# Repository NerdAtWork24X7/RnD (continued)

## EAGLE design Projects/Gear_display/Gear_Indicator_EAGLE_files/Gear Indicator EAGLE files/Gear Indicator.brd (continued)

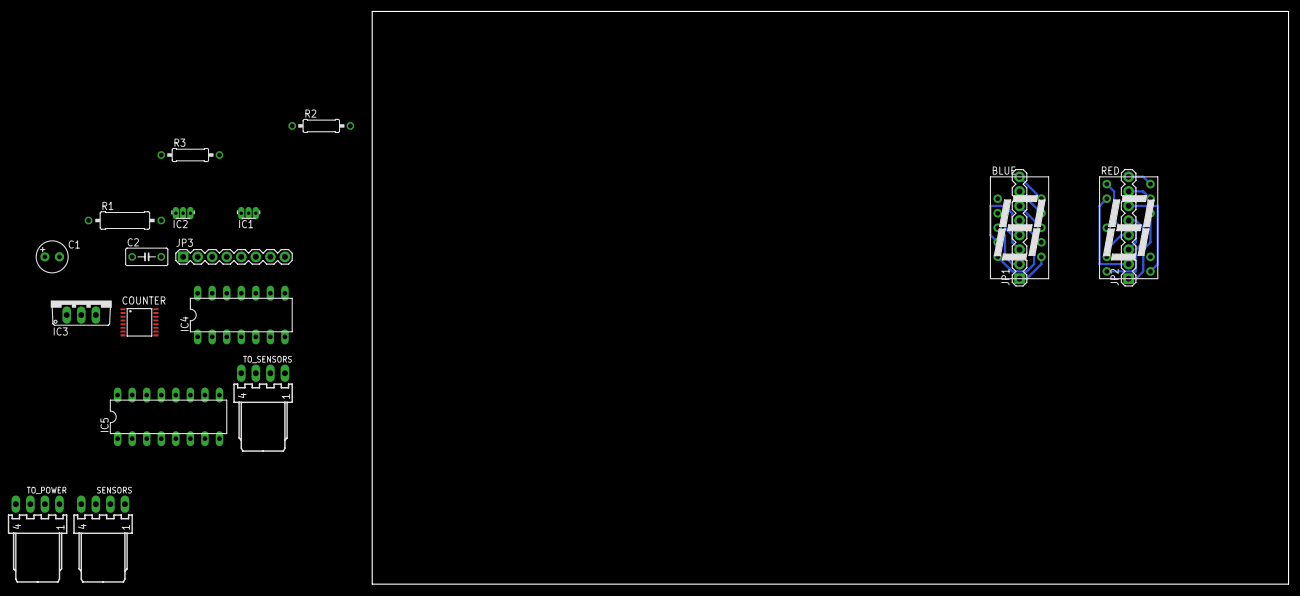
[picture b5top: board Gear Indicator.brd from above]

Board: 2 copper layers, 160.0 x 100.0 mm, 19 parts (0 on the bottom side), 38 nets.

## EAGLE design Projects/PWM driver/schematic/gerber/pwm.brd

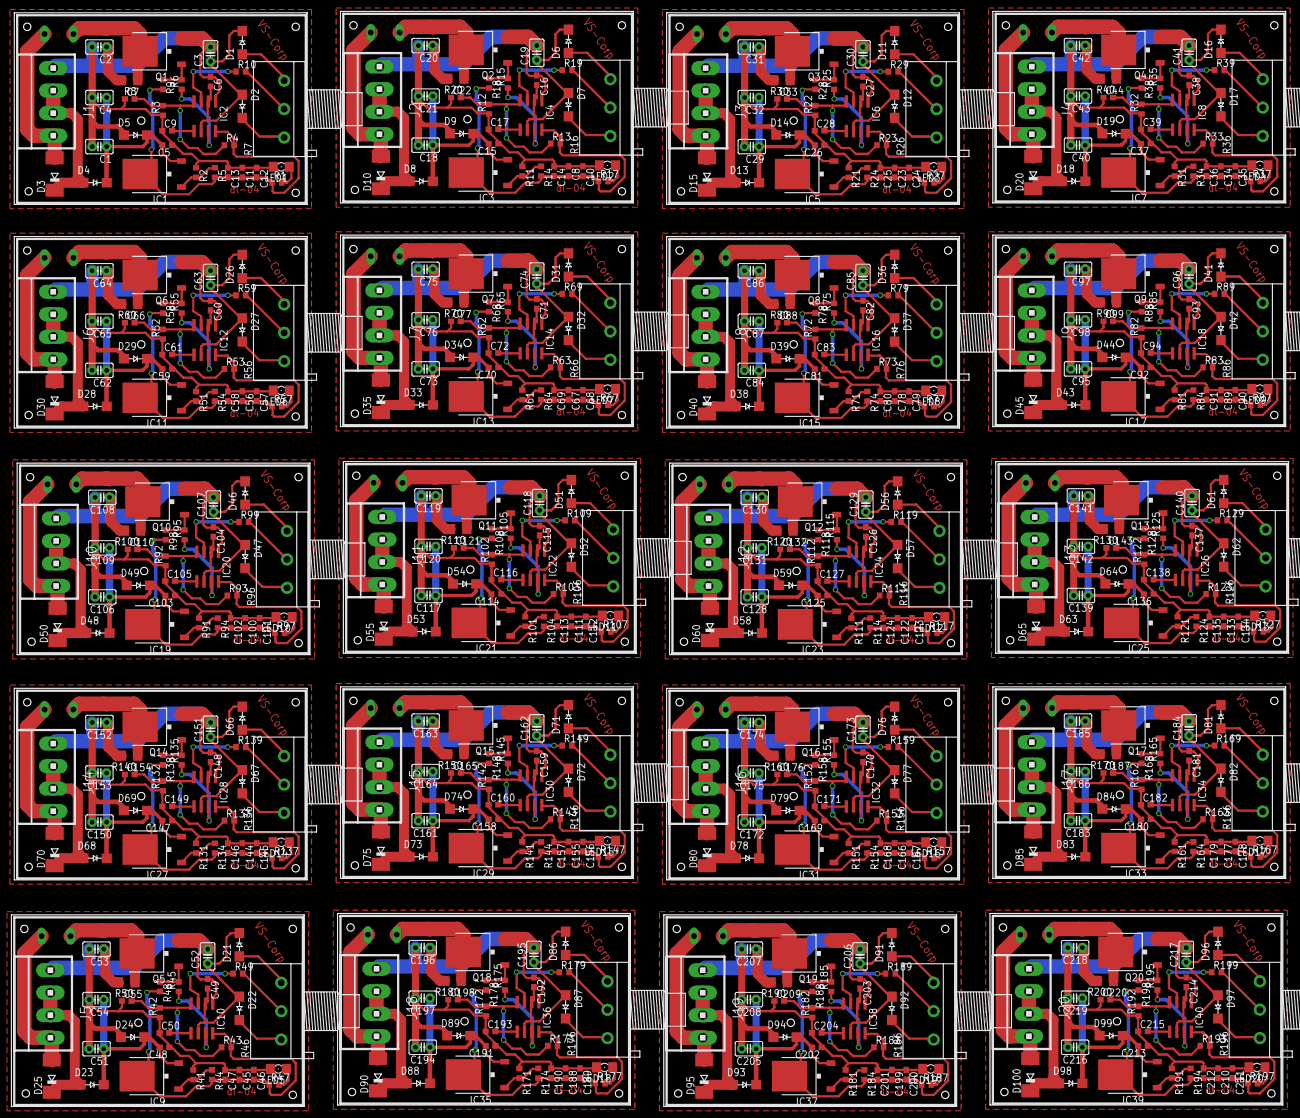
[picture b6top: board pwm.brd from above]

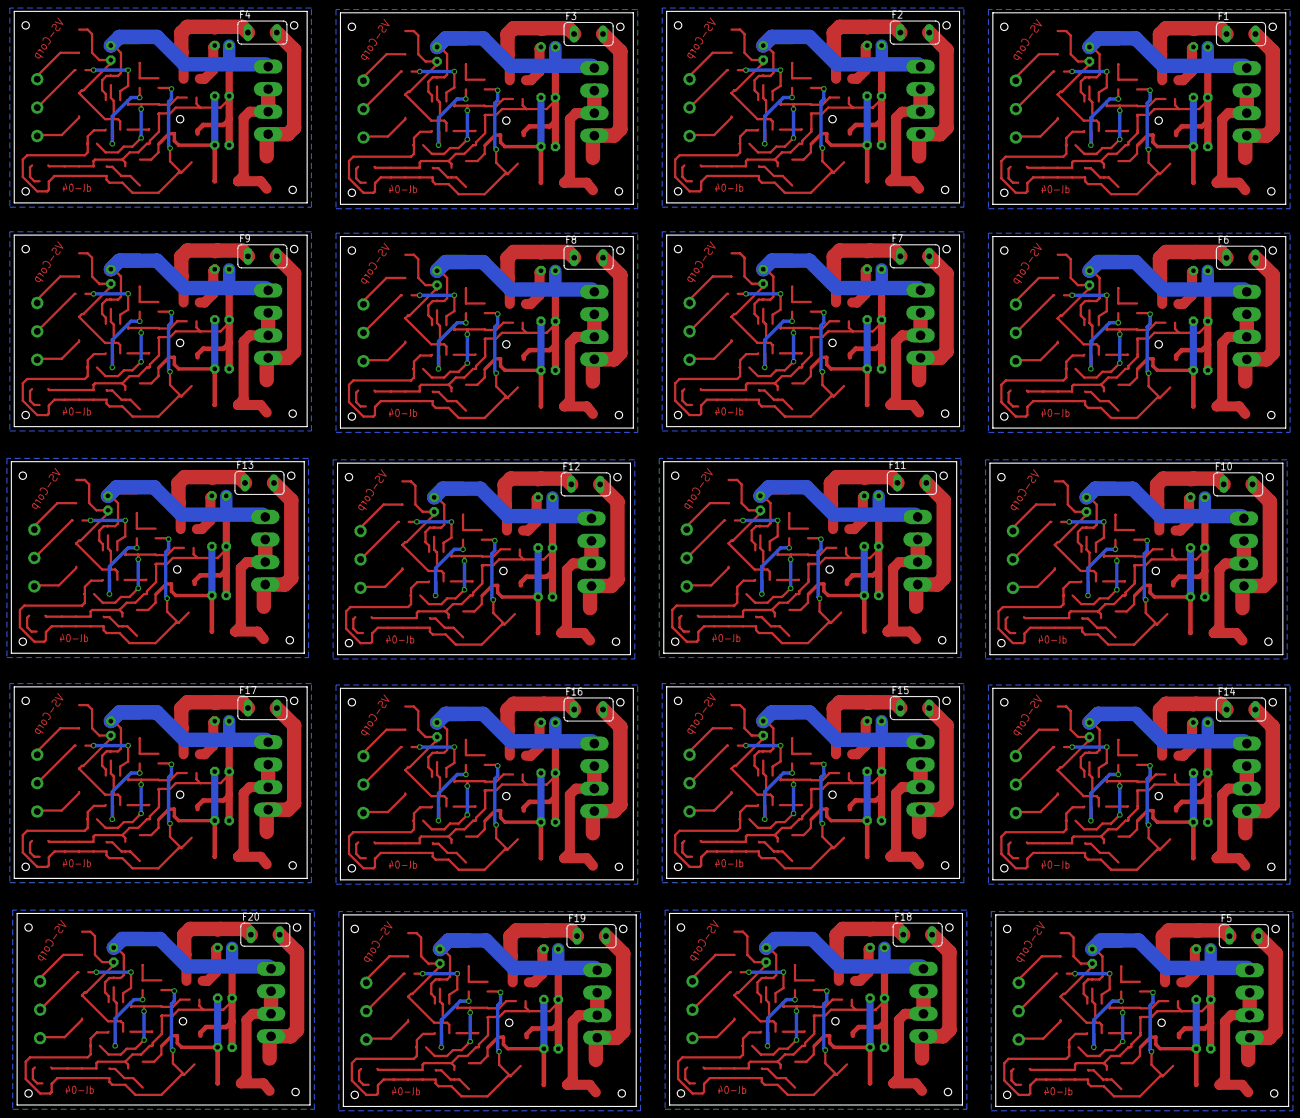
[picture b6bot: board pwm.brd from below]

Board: 2 copper layers, 224.8 x 192.7 mm, 640 parts (20 on the bottom side), 360 nets.

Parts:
C1, C18, C29, C40, C51, C62, C73, C84, C95, C106, C117, C128, C139, C150, C161, C172, C183, C194, C205, C216: C025-025X050
C2, C20, C31, C42, C53, C64, C75, C86, C97, C108, C119, C130, C141, C152, C163, C174, C185, C196, C207, C218: 2.2uf; C025-025X050
C3, C19, C30, C41, C52, C63, C74, C85, C96, C107, C118, C129, C140, C151, C162, C173, C184, C195, C206, C217: 0.1uf; C025-025X050
C4, C21, C32, C43, C54, C65, C76, C87, C98, C109, C120, C131, C142, C153, C164, C175, C186, C197, C208, C219: 220uf; C025-025X050
C5, C15, C26, C37, C48, C59, C70, C81, C92, C103, C114, C125, C136, C147, C158, C169, C180, C191, C202, C213: 100nf; C0603
C6, C16, C27, C38, C49, C60, C71, C82, C93, C104, C115, C126, C137, C148, C159, C170, C181, C192, C203, C214: 0.1uF; C0603
C7, C22, C33, C44, C55, C66, C77, C88, C99, C110, C121, C132, C143, C154, C165, C176, C187, C198, C209, C220: 220uf; C0603
C8, C11, C23, C34, C45, C56, C67, C78, C89, C100, C111, C122, C133, C144, C155, C166, C177, C188, C199, C210: 100nF; C0603
C9, C10, C12, C17, C24, C28, C35, C39, C46, C50, C57, C61, C68, C72, C79, C83, C90, C94, C101, C105, C112, C116, C123, C127, C134, C138, C145, C149, C156, C160, C167, C171, C178, C182, C189, C193, C200, C204, C211, C215: 10nF; C0603
C13, C14, C25, C36, C47, C58, C69, C80, C91, C102, C113, C124, C135, C146, C157, C168, C179, C190, C201, C212: 1uF; C0603
D1, D2, D6, D7, D11, D12, D16, D17, D21, D22, D26, D27, D31, D32, D36, D37, D41, D42, D46, D47, D51, D52, D56, D57, D61, D62, D66, D67, D71, D72, D76, D77, D81, D82, D86, D87, D91, D92, D96, D97: FM4007; SMA-DO214AC
D3, D10, D15, D20, D25, D30, D35, D40, D45, D50, D55, D60, D65, D70, D75, D80, D85, D90, D95, D100: SOD106-W
D4, D8, D13, D18, D23, D28, D33, D38, D43, D48, D53, D58, D63, D68, D73, D78, D83, D88, D93, D98: Fm4007; SMA-DO214AC
D5, D9, D14, D19, D24, D29, D34, D39, D44, D49, D54, D59, D64, D69, D74, D79, D84, D89, D94, D99: 1N34; SMA-DO214AC
F1, F2, F3, F4, F5, F6, F7, F8, F9, F10, F11, F12, F13, F14, F15, F16, F17, F18, F19, F20: FUSETE5; TE5
IC1, IC3, IC5, IC7, IC9, IC11, IC13, IC15, IC17, IC19, IC21, IC23, IC25, IC27, IC29, IC31, IC33, IC35, IC37, IC39: 317; DPACK
IC2, IC4, IC6, IC8, IC10, IC12, IC14, IC16, IC18, IC20, IC22, IC24, IC26, IC28, IC30, IC32, IC34, IC36, IC38, IC40: LM555D; SO08
J1, J2, J3, J4, J5, J6, J7, J8, J9, J10, J11, J12, J13, J14, J15, J16, J17, J18, J19, J20: 1X4MTA
LED1, LED2, LED3, LED4, LED5, LED6, LED7, LED8, LED9, LED10, LED11, LED12, LED13, LED14, LED15, LED16, LED17, LED18, LED19, LED20: LED_1206
Q1, Q2, Q3, Q4, Q5, Q6, Q7, Q8, Q9, Q10, Q11, Q12, Q13, Q14, Q15, Q16, Q17, Q18, Q19, Q20: FDD4141TO252; TO252
R1, R5, R14, R17, R24, R27, R34, R37, R44, R47, R54, R57, R64, R67, R74, R77, R84, R87, R94, R97, R104, R107, R114, R117, R124, R127, R134, R137, R144, R147, R154, R157, R164, R167, R174, R177, R184, R187, R194, R197: 470; R0603
R2, R11, R21, R31, R41, R51, R61, R71, R81, R91, R101, R111, R121, R131, R141, R151, R161, R171, R181, R191: 1.5k; R0603
R3, R12, R22, R32, R42, R52, R62, R72, R82, R92, R102, R112, R122, R132, R142, R152, R162, R172, R182, R192: 330k; R0603
R4, R13, R23, R33, R43, R53, R63, R73, R83, R93, R103, R113, R123, R133, R143, R153, R163, R173, R183, R193: 150k; R0603
R6, R15, R25, R35, R45, R55, R65, R75, R85, R95, R105, R115, R125, R135, R145, R155, R165, R175, R185, R195: 1k; R0603
R7, R16, R26, R36, R46, R56, R66, R76, R86, R96, R106, R116, R126, R136, R146, R156, R166, R176, R186, R196: 3RP/1610N
R8, R20, R30, R40, R50, R60, R70, R80, R90, R100, R110, R120, R130, R140, R150, R160, R170, R180, R190, R200: 100; R1206
R9, R18, R28, R38, R48, R58, R68, R78, R88, R98, R108, R118, R128, R138, R148, R158, R168, R178, R188, R198: 47k; R0603
R10, R19, R29, R39, R49, R59, R69, R79, R89, R99, R109, R119, R129, R139, R149, R159, R169, R179, R189, R199: 0r0; R0603

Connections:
GND: C1.2, C2.2, C3.2, C4.2, C5.1, C6.1, C7.1, C9.1, C11.1, C12.1, C13.1, D5.A, IC2.1, J1.1, LED1.C, Q1.2, R2.1, R3.1
GND1: C8.1, C10.1, C14.1, C15.1, C16.1, C17.1, C18.2, C19.2, C20.2, C21.2, C22.1, D9.A, IC4.1, J2.1, LED2.C, Q2.2, R11.1, R12.1
GND2: C23.1, C24.1, C25.1, C26.1, C27.1, C28.1, C29.2, C30.2, C31.2, C32.2, C33.1, D14.A, IC6.1, J3.1, LED3.C, Q3.2, R21.1, R22.1
GND3: C34.1, C35.1, C36.1, C37.1, C38.1, C39.1, C40.2, C41.2, C42.2, C43.2, C44.1, D19.A, IC8.1, J4.1, LED4.C, Q4.2, R31.1, R32.1
GND4: C45.1, C46.1, C47.1, C48.1, C49.1, C50.1, C51.2, C52.2, C53.2, C54.2, C55.1, D24.A, IC10.1, J5.1, LED5.C, Q5.2, R41.1, R42.1
GND5: C56.1, C57.1, C58.1, C59.1, C60.1, C61.1, C62.2, C63.2, C64.2, C65.2, C66.1, D29.A, IC12.1, J6.1, LED6.C, Q6.2, R51.1, R52.1
GND6: C67.1, C68.1, C69.1, C70.1, C71.1, C72.1, C73.2, C74.2, C75.2, C76.2, C77.1, D34.A, IC14.1, J7.1, LED7.C, Q7.2, R61.1, R62.1
GND7: C78.1, C79.1, C80.1, C81.1, C82.1, C83.1, C84.2, C85.2, C86.2, C87.2, C88.1, D39.A, IC16.1, J8.1, LED8.C, Q8.2, R71.1, R72.1
GND8: C89.1, C90.1, C91.1, C92.1, C93.1, C94.1, C95.2, C96.2, C97.2, C98.2, C99.1, D44.A, IC18.1, J9.1, LED9.C, Q9.2, R81.1, R82.1
GND9: C100.1, C101.1, C102.1, C103.1, C104.1, C105.1, C106.2, C107.2, C108.2, C109.2, C110.1, D49.A, IC20.1, J10.1, LED10.C, Q10.2, R91.1, R92.1
GND10: C111.1, C112.1, C113.1, C114.1, C115.1, C116.1, C117.2, C118.2, C119.2, C120.2, C121.1, D54.A, IC22.1, J11.1, LED11.C, Q11.2, R101.1, R102.1
GND11: C122.1, C123.1, C124.1, C125.1, C126.1, C127.1, C128.2, C129.2, C130.2, C131.2, C132.1, D59.A, IC24.1, J12.1, LED12.C, Q12.2, R111.1, R112.1
GND12: C133.1, C134.1, C135.1, C136.1, C137.1, C138.1, C139.2, C140.2, C141.2, C142.2, C143.1, D64.A, IC26.1, J13.1, LED13.C, Q13.2, R121.1, R122.1
GND13: C144.1, C145.1, C146.1, C147.1, C148.1, C149.1, C150.2, C151.2, C152.2, C153.2, C154.1, D69.A, IC28.1, J14.1, LED14.C, Q14.2, R131.1, R132.1
GND14: C155.1, C156.1, C157.1, C158.1, C159.1, C160.1, C161.2, C162.2, C163.2, C164.2, C165.1, D74.A, IC30.1, J15.1, LED15.C, Q15.2, R141.1, R142.1
GND15: C166.1, C167.1, C168.1, C169.1, C170.1, C171.1, C172.2, C173.2, C174.2, C175.2, C176.1, D79.A, IC32.1, J16.1, LED16.C, Q16.2, R151.1, R152.1
GND16: C177.1, C178.1, C179.1, C180.1, C181.1, C182.1, C183.2, C184.2, C185.2, C186.2, C187.1, D84.A, IC34.1, J17.1, LED17.C, Q17.2, R161.1, R162.1
GND17: C188.1, C189.1, C190.1, C191.1, C192.1, C193.1, C194.2, C195.2, C196.2, C197.2, C198.1, D89.A, IC36.1, J18.1, LED18.C, Q18.2, R171.1, R172.1
GND18: C199.1, C200.1, C201.1, C202.1, C203.1, C204.1, C205.2, C206.2, C207.2, C208.2, C209.1, D94.A, IC38.1, J19.1, LED19.C, Q19.2, R181.1, R182.1
GND19: C210.1, C211.1, C212.1, C213.1, C214.1, C215.1, C216.2, C217.2, C218.2, C219.2, C220.1, D99.A, IC40.1, J20.1, LED20.C, Q20.2, R191.1, R192.1
unnamed: C7.2, IC2.4, R3.2, R4.1
unnamed: C3.1, C6.2, D1.K, D2.A, IC2.2, IC2.6
unnamed: D1.A, R7.3
unnamed: D2.K, R7.1
unnamed: R7.2, R10.2
unnamed: IC2.3, R10.1
unnamed: C9.2, IC2.5
unnamed: C1.1, C4.1, C5.2, D4.K, D5.K, IC1.VIN
unnamed: Q1.1, R6.2, R9.1
unnamed: IC2.7, R6.1
unnamed: LED1.A, R1.2
unnamed: C2.1, R8.2
unnamed: IC1.ADJ, R2.2, R5.1
unnamed: F1.1, Q1.3, R8.1
unnamed: D3.A, F1.2, J1.4
unnamed: D6.A, R16.3
unnamed: D7.K, R16.1
unnamed: C17.2, IC4.5
unnamed: C16.2, C19.1, D6.K, D7.A, IC4.2, IC4.6
unnamed: Q2.1, R15.2, R18.1
unnamed: C22.2, IC4.4, R12.2, R13.1
unnamed: IC4.3, R19.1
unnamed: IC4.7, R15.1
unnamed: C15.2, C18.1, C21.1, D8.K, D9.K, IC3.VIN
unnamed: LED2.A, R17.2
unnamed: IC3.ADJ, R11.2, R14.1
unnamed: F2.1, Q2.3, R20.1
unnamed: D10.A, F2.2, J2.4
unnamed: R16.2, R19.2
unnamed: C20.1, R20.2
unnamed: D11.A, R26.3
unnamed: D12.K, R26.1
unnamed: C28.2, IC6.5
unnamed: C27.2, C30.1, D11.K, D12.A, IC6.2, IC6.6
unnamed: Q3.1, R25.2, R28.1
unnamed: C33.2, IC6.4, R22.2, R23.1
unnamed: IC6.3, R29.1
unnamed: IC6.7, R25.1
unnamed: C26.2, C29.1, C32.1, D13.K, D14.K, IC5.VIN
unnamed: LED3.A, R27.2
unnamed: IC5.ADJ, R21.2, R24.1
unnamed: F3.1, Q3.3, R30.1
unnamed: D15.A, F3.2, J3.4
unnamed: R26.2, R29.2
unnamed: C31.1, R30.2
unnamed: D16.A, R36.3
unnamed: D17.K, R36.1
unnamed: C39.2, IC8.5
unnamed: C38.2, C41.1, D16.K, D17.A, IC8.2, IC8.6
unnamed: Q4.1, R35.2, R38.1
unnamed: C44.2, IC8.4, R32.2, R33.1
unnamed: IC8.3, R39.1
unnamed: IC8.7, R35.1
unnamed: C37.2, C40.1, C43.1, D18.K, D19.K, IC7.VIN
unnamed: LED4.A, R37.2
unnamed: IC7.ADJ, R31.2, R34.1
unnamed: F4.1, Q4.3, R40.1
unnamed: D20.A, F4.2, J4.4
unnamed: R36.2, R39.2
unnamed: C42.1, R40.2
unnamed: D21.A, R46.3
unnamed: D22.K, R46.1
unnamed: C50.2, IC10.5
unnamed: C49.2, C52.1, D21.K, D22.A, IC10.2, IC10.6
unnamed: Q5.1, R45.2, R48.1
unnamed: C55.2, IC10.4, R42.2, R43.1
unnamed: IC10.3, R49.1
unnamed: IC10.7, R45.1
unnamed: C48.2, C51.1, C54.1, D23.K, D24.K, IC9.VIN
unnamed: LED5.A, R47.2
unnamed: IC9.ADJ, R41.2, R44.1
unnamed: F5.1, Q5.3, R50.1
unnamed: D25.A, F5.2, J5.4
unnamed: R46.2, R49.2
unnamed: C53.1, R50.2
unnamed: D26.A, R56.3
unnamed: D27.K, R56.1
unnamed: C61.2, IC12.5
unnamed: C60.2, C63.1, D26.K, D27.A, IC12.2, IC12.6
unnamed: Q6.1, R55.2, R58.1
unnamed: C66.2, IC12.4, R52.2, R53.1
unnamed: IC12.3, R59.1
unnamed: IC12.7, R55.1
unnamed: C59.2, C62.1, C65.1, D28.K, D29.K, IC11.VIN
unnamed: LED6.A, R57.2
unnamed: IC11.ADJ, R51.2, R54.1
unnamed: F6.1, Q6.3, R60.1
unnamed: D30.A, F6.2, J6.4
unnamed: R56.2, R59.2
unnamed: C64.1, R60.2
unnamed: D31.A, R66.3
unnamed: D32.K, R66.1
unnamed: C72.2, IC14.5
unnamed: C71.2, C74.1, D31.K, D32.A, IC14.2, IC14.6
unnamed: Q7.1, R65.2, R68.1
unnamed: C77.2, IC14.4, R62.2, R63.1
unnamed: IC14.3, R69.1
unnamed: IC14.7, R65.1
unnamed: C70.2, C73.1, C76.1, D33.K, D34.K, IC13.VIN
unnamed: LED7.A, R67.2
unnamed: IC13.ADJ, R61.2, R64.1
unnamed: F7.1, Q7.3, R70.1
unnamed: D35.A, F7.2, J7.4
unnamed: R66.2, R69.2
unnamed: C75.1, R70.2
unnamed: D36.A, R76.3
unnamed: D37.K, R76.1
unnamed: C83.2, IC16.5
unnamed: C82.2, C85.1, D36.K, D37.A, IC16.2, IC16.6
unnamed: Q8.1, R75.2, R78.1
unnamed: C88.2, IC16.4, R72.2, R73.1
unnamed: IC16.3, R79.1
unnamed: IC16.7, R75.1
unnamed: C81.2, C84.1, C87.1, D38.K, D39.K, IC15.VIN
unnamed: LED8.A, R77.2
unnamed: IC15.ADJ, R71.2, R74.1
unnamed: F8.1, Q8.3, R80.1
unnamed: D40.A, F8.2, J8.4
unnamed: R76.2, R79.2
unnamed: C86.1, R80.2
unnamed: D41.A, R86.3
unnamed: D42.K, R86.1
unnamed: C94.2, IC18.5
unnamed: C93.2, C96.1, D41.K, D42.A, IC18.2, IC18.6
unnamed: Q9.1, R85.2, R88.1
unnamed: C99.2, IC18.4, R82.2, R83.1
unnamed: IC18.3, R89.1
unnamed: IC18.7, R85.1
unnamed: C92.2, C95.1, C98.1, D43.K, D44.K, IC17.VIN
unnamed: LED9.A, R87.2
unnamed: IC17.ADJ, R81.2, R84.1
unnamed: F9.1, Q9.3, R90.1
unnamed: D45.A, F9.2, J9.4
unnamed: D46.A, R96.3
unnamed: D47.K, R96.1
unnamed: C105.2, IC20.5
unnamed: C104.2, C107.1, D46.K, D47.A, IC20.2, IC20.6
unnamed: Q10.1, R95.2, R98.1
unnamed: C110.2, IC20.4, R92.2, R93.1
unnamed: IC20.3, R99.1
unnamed: IC20.7, R95.1
unnamed: C103.2, C106.1, C109.1, D48.K, D49.K, IC19.VIN
unnamed: LED10.A, R97.2
unnamed: IC19.ADJ, R91.2, R94.1
unnamed: F10.1, Q10.3, R100.1
unnamed: D50.A, F10.2, J10.4
unnamed: R96.2, R99.2
unnamed: C108.1, R100.2
unnamed: D51.A, R106.3
unnamed: D52.K, R106.1
unnamed: C116.2, IC22.5
unnamed: C115.2, C118.1, D51.K, D52.A, IC22.2, IC22.6
unnamed: Q11.1, R105.2, R108.1
unnamed: C121.2, IC22.4, R102.2, R103.1
unnamed: IC22.3, R109.1
unnamed: IC22.7, R105.1
unnamed: C114.2, C117.1, C120.1, D53.K, D54.K, IC21.VIN
unnamed: LED11.A, R107.2
unnamed: IC21.ADJ, R101.2, R104.1
unnamed: F11.1, Q11.3, R110.1
unnamed: D55.A, F11.2, J11.4
unnamed: R106.2, R109.2
unnamed: C119.1, R110.2
unnamed: R86.2, R89.2
unnamed: C97.1, R90.2
unnamed: D56.A, R116.3
unnamed: D57.K, R116.1
unnamed: C127.2, IC24.5
unnamed: C126.2, C129.1, D56.K, D57.A, IC24.2, IC24.6
unnamed: Q12.1, R115.2, R118.1
unnamed: C132.2, IC24.4, R112.2, R113.1
unnamed: IC24.3, R119.1
unnamed: IC24.7, R115.1
unnamed: C125.2, C128.1, C131.1, D58.K, D59.K, IC23.VIN
unnamed: LED12.A, R117.2
unnamed: IC23.ADJ, R111.2, R114.1
unnamed: F12.1, Q12.3, R120.1
unnamed: D60.A, F12.2, J12.4
unnamed: R116.2, R119.2
unnamed: C130.1, R120.2
unnamed: D61.A, R126.3
unnamed: D62.K, R126.1
unnamed: C138.2, IC26.5
unnamed: C137.2, C140.1, D61.K, D62.A, IC26.2, IC26.6
unnamed: Q13.1, R125.2, R128.1
unnamed: C143.2, IC26.4, R122.2, R123.1
unnamed: IC26.3, R129.1
unnamed: IC26.7, R125.1
unnamed: C136.2, C139.1, C142.1, D63.K, D64.K, IC25.VIN
unnamed: LED13.A, R127.2
unnamed: IC25.ADJ, R121.2, R124.1
unnamed: D66.A, R136.3
unnamed: D67.K, R136.1
unnamed: C149.2, IC28.5
unnamed: C148.2, C151.1, D66.K, D67.A, IC28.2, IC28.6
unnamed: Q14.1, R135.2, R138.1
unnamed: C154.2, IC28.4, R132.2, R133.1
unnamed: IC28.3, R139.1
unnamed: IC28.7, R135.1
unnamed: C147.2, C150.1, C153.1, D68.K, D69.K, IC27.VIN
unnamed: LED14.A, R137.2
unnamed: IC27.ADJ, R131.2, R134.1
unnamed: F14.1, Q14.3, R140.1
unnamed: D70.A, F14.2, J14.4
unnamed: R136.2, R139.2
unnamed: C152.1, R140.2
unnamed: D71.A, R146.3
unnamed: D72.K, R146.1
unnamed: C160.2, IC30.5
unnamed: C159.2, C162.1, D71.K, D72.A, IC30.2, IC30.6
unnamed: Q15.1, R145.2, R148.1
unnamed: C165.2, IC30.4, R142.2, R143.1
unnamed: IC30.3, R149.1
unnamed: IC30.7, R145.1
unnamed: C158.2, C161.1, C164.1, D73.K, D74.K, IC29.VIN
unnamed: LED15.A, R147.2
unnamed: IC29.ADJ, R141.2, R144.1
unnamed: F15.1, Q15.3, R150.1
unnamed: D75.A, F15.2, J15.4
unnamed: R146.2, R149.2
unnamed: C163.1, R150.2
unnamed: F13.1, Q13.3, R130.1
unnamed: D65.A, F13.2, J13.4
unnamed: R126.2, R129.2
unnamed: C141.1, R130.2
unnamed: D76.A, R156.3
unnamed: D77.K, R156.1
unnamed: C171.2, IC32.5
unnamed: C170.2, C173.1, D76.K, D77.A, IC32.2, IC32.6
unnamed: Q16.1, R155.2, R158.1
unnamed: C176.2, IC32.4, R152.2, R153.1
unnamed: IC32.3, R159.1
unnamed: IC32.7, R155.1
unnamed: C169.2, C172.1, C175.1, D78.K, D79.K, IC31.VIN
unnamed: LED16.A, R157.2
unnamed: IC31.ADJ, R151.2, R154.1
unnamed: F16.1, Q16.3, R160.1
unnamed: D80.A, F16.2, J16.4
unnamed: R156.2, R159.2
unnamed: C174.1, R160.2
unnamed: D81.A, R166.3
unnamed: D82.K, R166.1
unnamed: C182.2, IC34.5
unnamed: C181.2, C184.1, D81.K, D82.A, IC34.2, IC34.6
unnamed: Q17.1, R165.2, R168.1
unnamed: C187.2, IC34.4, R162.2, R163.1
unnamed: IC34.3, R169.1
unnamed: IC34.7, R165.1
unnamed: C180.2, C183.1, C186.1, D83.K, D84.K, IC33.VIN
unnamed: D86.A, R176.3
unnamed: D87.K, R176.1
unnamed: C193.2, IC36.5
unnamed: C192.2, C195.1, D86.K, D87.A, IC36.2, IC36.6
unnamed: Q18.1, R175.2, R178.1
unnamed: C198.2, IC36.4, R172.2, R173.1
unnamed: IC36.3, R179.1
unnamed: IC36.7, R175.1
unnamed: C191.2, C194.1, C197.1, D88.K, D89.K, IC35.VIN
unnamed: LED18.A, R177.2
unnamed: IC35.ADJ, R171.2, R174.1
unnamed: F18.1, Q18.3, R180.1
unnamed: D90.A, F18.2, J18.4
unnamed: R176.2, R179.2
unnamed: C196.1, R180.2
unnamed: LED17.A, R167.2
unnamed: IC33.ADJ, R161.2, R164.1
unnamed: F17.1, Q17.3, R170.1
unnamed: D85.A, F17.2, J17.4
unnamed: R166.2, R169.2
unnamed: C185.1, R170.2
unnamed: D91.A, R186.3
unnamed: D92.K, R186.1
unnamed: C204.2, IC38.5
unnamed: C203.2, C206.1, D91.K, D92.A, IC38.2, IC38.6
unnamed: Q19.1, R185.2, R188.1
unnamed: C209.2, IC38.4, R182.2, R183.1
unnamed: IC38.3, R189.1
unnamed: IC38.7, R185.1
unnamed: C202.2, C205.1, C208.1, D93.K, D94.K, IC37.VIN
unnamed: LED19.A, R187.2
unnamed: IC37.ADJ, R181.2, R184.1
unnamed: F19.1, Q19.3, R190.1
unnamed: D95.A, F19.2, J19.4
unnamed: R186.2, R189.2
unnamed: C207.1, R190.2
unnamed: D96.A, R196.3
unnamed: D97.K, R196.1
unnamed: C215.2, IC40.5
unnamed: C214.2, C217.1, D96.K, D97.A, IC40.2, IC40.6
unnamed: Q20.1, R195.2, R198.1
unnamed: C220.2, IC40.4, R192.2, R193.1
unnamed: IC40.3, R199.1
unnamed: IC40.7, R195.1
unnamed: C213.2, C216.1, C219.1, D98.K, D99.K, IC39.VIN
unnamed: LED20.A, R197.2
unnamed: IC39.ADJ, R191.2, R194.1
unnamed: F20.1, Q20.3, R200.1
unnamed: D100.A, F20.2, J20.4
unnamed: R196.2, R199.2
unnamed: C218.1, R200.2
VCC: C11.2, C12.2, C13.2, IC1.VOUT, IC2.8, R1.1, R4.2, R5.2, R9.2
VCC1: C8.2, C10.2, C14.2, IC3.VOUT, IC4.8, R13.2, R14.2, R17.1, R18.2
VCC2: C23.2, C24.2, C25.2, IC5.VOUT, IC6.8, R23.2, R24.2, R27.1, R28.2
VCC3: C34.2, C35.2, C36.2, IC7.VOUT, IC8.8, R33.2, R34.2, R37.1, R38.2
VCC4: C45.2, C46.2, C47.2, IC9.VOUT, IC10.8, R43.2, R44.2, R47.1, R48.2
VCC5: C56.2, C57.2, C58.2, IC11.VOUT, IC12.8, R53.2, R54.2, R57.1, R58.2
VCC6: C67.2, C68.2, C69.2, IC13.VOUT, IC14.8, R63.2, R64.2, R67.1, R68.2
VCC7: C78.2, C79.2, C80.2, IC15.VOUT, IC16.8, R73.2, R74.2, R77.1, R78.2
VCC8: C89.2, C90.2, C91.2, IC17.VOUT, IC18.8, R83.2, R84.2, R87.1, R88.2
VCC9: C100.2, C101.2, C102.2, IC19.VOUT, IC20.8, R93.2, R94.2, R97.1, R98.2
VCC10: C111.2, C112.2, C113.2, IC21.VOUT, IC22.8, R103.2, R104.2, R107.1, R108.2
VCC11: C122.2, C123.2, C124.2, IC23.VOUT, IC24.8, R113.2, R114.2, R117.1, R118.2
VCC12: C133.2, C134.2, C135.2, IC25.VOUT, IC26.8, R123.2, R124.2, R127.1, R128.2
VCC13: C144.2, C145.2, C146.2, IC27.VOUT, IC28.8, R133.2, R134.2, R137.1, R138.2
VCC14: C155.2, C156.2, C157.2, IC29.VOUT, IC30.8, R143.2, R144.2, R147.1, R148.2
VCC15: C166.2, C167.2, C168.2, IC31.VOUT, IC32.8, R153.2, R154.2, R157.1, R158.2
VCC16: C177.2, C178.2, C179.2, IC33.VOUT, IC34.8, R163.2, R164.2, R167.1, R168.2
VCC17: C188.2, C189.2, C190.2, IC35.VOUT, IC36.8, R173.2, R174.2, R177.1, R178.2
VCC18: C199.2, C200.2, C201.2, IC37.VOUT, IC38.8, R183.2, R184.2, R187.1, R188.2
VCC19: C210.2, C211.2, C212.2, IC39.VOUT, IC40.8, R193.2, R194.2, R197.1, R198.2
VDD: D3.C, D4.A, J1.2, J1.3
VDD1: D8.A, D10.C, J2.2, J2.3
VDD2: D13.A, D15.C, J3.2, J3.3
VDD3: D18.A, D20.C, J4.2, J4.3
VDD4: D23.A, D25.C, J5.2, J5.3
VDD5: D28.A, D30.C, J6.2, J6.3
VDD6: D33.A, D35.C, J7.2, J7.3
VDD7: D38.A, D40.C, J8.2, J8.3
VDD8: D43.A, D45.C, J9.2, J9.3
VDD9: D48.A, D50.C, J10.2, J10.3
VDD10: D53.A, D55.C, J11.2, J11.3
VDD11: D58.A, D60.C, J12.2, J12.3
VDD12: D63.A, D65.C, J13.2, J13.3
VDD13: D68.A, D70.C, J14.2, J14.3
VDD14: D73.A, D75.C, J15.2, J15.3
VDD15: D78.A, D80.C, J16.2, J16.3
VDD16: D83.A, D85.C, J17.2, J17.3
VDD17: D88.A, D90.C, J18.2, J18.3
VDD18: D93.A, D95.C, J19.2, J19.3
VDD19: D98.A, D100.C, J20.2, J20.3
